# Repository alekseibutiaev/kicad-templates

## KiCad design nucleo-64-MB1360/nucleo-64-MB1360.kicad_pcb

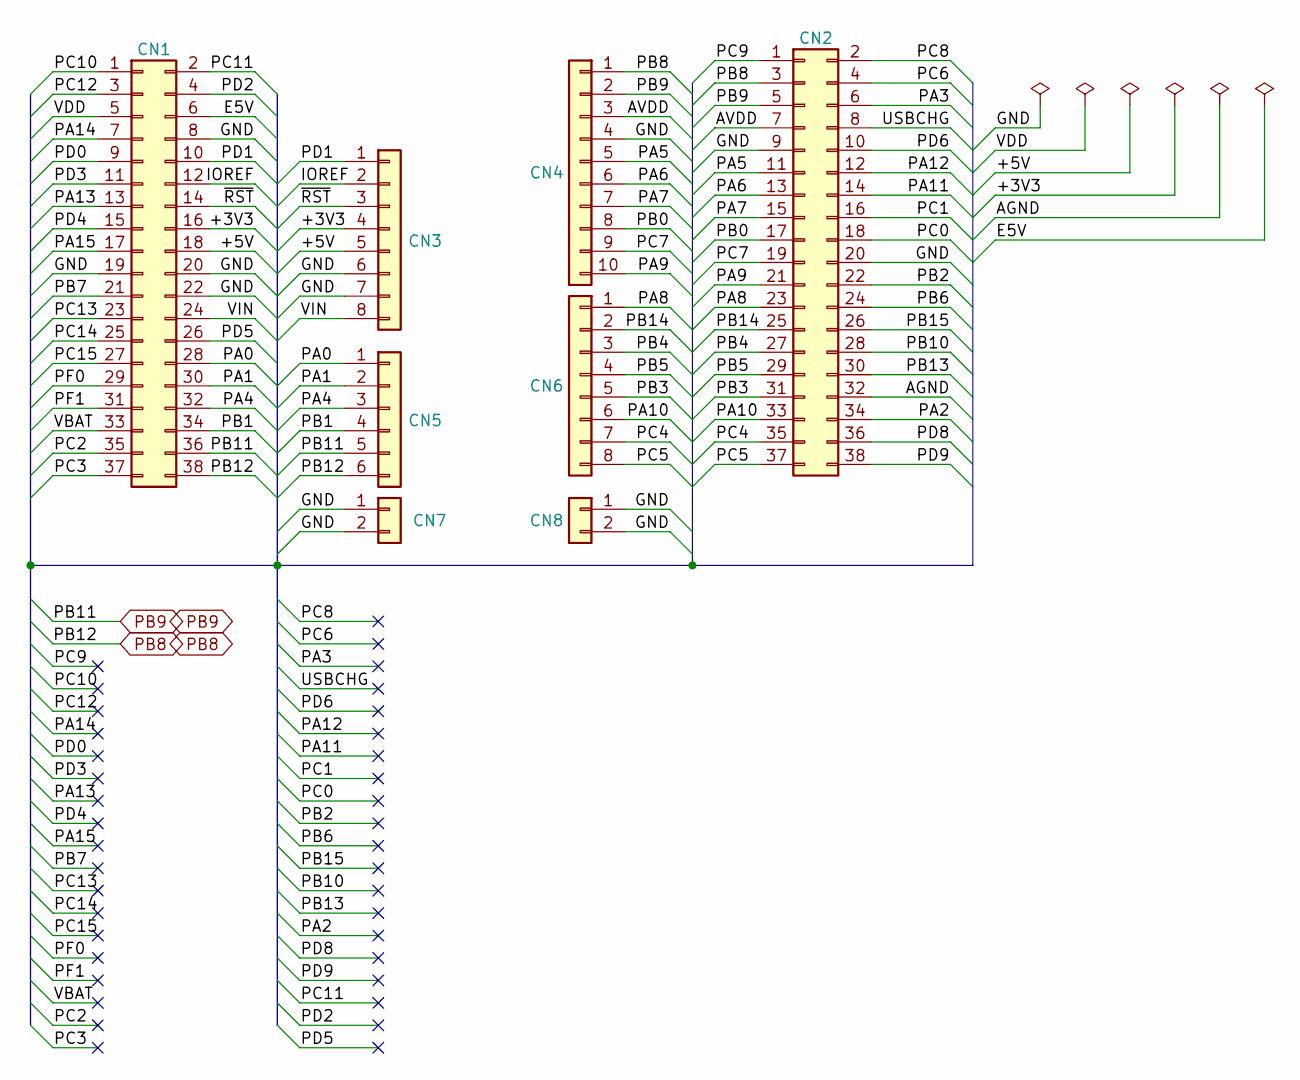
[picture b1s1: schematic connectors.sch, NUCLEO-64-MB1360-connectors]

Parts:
CN1, CN2: Conn_02x19_Odd_Even; PinHeader_2x19_P2.54mm_Vertical
CN3, CN6: Conn_01x08; PinSocket_1x08_P2.54mm_Vertical
CN4: Conn_01x10; PinSocket_1x10_P2.54mm_Vertical
CN5: Conn_01x06; PinSocket_1x06_P2.54mm_Vertical
CN7, CN8: Conn_01x02; PinHeader_1x02_P2.54mm_Vertical

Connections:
/connectors/+3V3: CN1.16, CN3.4
/connectors/+5V: CN1.18, CN3.5
/connectors/AGND: CN2.32
/connectors/AVDD: CN2.7, CN4.3
/connectors/E5V: CN1.6
/connectors/GND: CN1.8, CN1.19, CN1.20, CN1.22, CN2.9, CN2.20, CN3.6, CN3.7, CN4.4, CN7.1, CN7.2, CN8.1, CN8.2
/connectors/IOREF: CN1.12, CN3.2
/connectors/PA0: CN1.28, CN5.1
/connectors/PA1: CN1.30, CN5.2
/connectors/PA2: CN2.34
/connectors/PA3: CN2.6
/connectors/PA4: CN1.32, CN5.3
/connectors/PA5: CN2.11, CN4.5
/connectors/PA6: CN2.13, CN4.6
/connectors/PA7: CN2.15, CN4.7
/connectors/PA8: CN2.23, CN6.1
/connectors/PA9: CN2.21, CN4.10
/connectors/PA10: CN2.33, CN6.6
/connectors/PA11: CN2.14
/connectors/PA12: CN2.12
/connectors/PA13: CN1.13
/connectors/PA14: CN1.7
/connectors/PA15: CN1.17
/connectors/PB0: CN2.17, CN4.8
/connectors/PB1: CN1.34, CN5.4
/connectors/PB2: CN2.22
/connectors/PB3: CN2.31, CN6.5
/connectors/PB4: CN2.27, CN6.3
/connectors/PB5: CN2.29, CN6.4
/connectors/PB6: CN2.24
/connectors/PB7: CN1.21
/connectors/PB10: CN2.28
/connectors/PB13: CN2.30
/connectors/PB14: CN2.25, CN6.2
/connectors/PB15: CN2.26
/connectors/PC0: CN2.18
/connectors/PC1: CN2.16
/connectors/PC2: CN1.35
/connectors/PC3: CN1.37
/connectors/PC4: CN2.35, CN6.7
/connectors/PC5: CN2.37, CN6.8
/connectors/PC6: CN2.4
/connectors/PC7: CN2.19, CN4.9
/connectors/PC8: CN2.2
/connectors/PC9: CN2.1
/connectors/PC10: CN1.1
/connectors/PC11: CN1.2
/connectors/PC12: CN1.3
/connectors/PC13: CN1.23
/connectors/PC14: CN1.25
/connectors/PC15: CN1.27
/connectors/PD0: CN1.9
/connectors/PD1: CN1.10, CN3.1
/connectors/PD2: CN1.4
/connectors/PD3: CN1.11
/connectors/PD4: CN1.15
/connectors/PD5: CN1.26
/connectors/PD6: CN2.10
/connectors/PD8: CN2.36
/connectors/PD9: CN2.38
/connectors/PF0: CN1.29
/connectors/PF1: CN1.31
/connectors/USBCHG: CN2.8
/connectors/VBAT: CN1.33
/connectors/VDD: CN1.5
/connectors/VIN: CN1.24, CN3.8
/connectors/~RST: CN1.14, CN3.3
PB8: CN1.38, CN2.3, CN4.1, CN5.6
PB9: CN1.36, CN2.5, CN4.2, CN5.5

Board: 2 copper layers, 8 parts (0 on the bottom side), 28 nets, no tracks yet.

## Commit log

2021-01-31 add template nucleo-32-MB1180 and nucleo-64-MB1360
2021-01-31 set position for connectors
2021-01-31 add info for MC1360
2021-01-31 improve nucleo-64-MB136
